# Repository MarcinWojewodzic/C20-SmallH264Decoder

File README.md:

# C20 — H.264 decoding on STM32

C20 is an embedded video project built around a custom STM32H753 board and a software H.264/AVC decoder written from scratch. The first goal is to decode a short, low-resolution clip and display it on the board's LCD. From there, the project will measure how far the Cortex-M7 and external SDRAM can take it.

**Project status:** KiCad hardware design and STM32Cube firmware scaffolding are in the repository. The H.264 decoder and playback pipeline are planned.

## Hardware

Board revision **C20W1B1V1.0** pairs the STM32H753 with external SDRAM for decoded pictures and display buffers, and a touch display driven by the MCU's LCD controller.

| Subsystem | Schematic design |
| --- | --- |
| Microcontroller | STM32H753IITx, Arm Cortex-M7, with an STDC14 debug connector |
| Working memory | 16 MiB ISSI IS45S32400J SDR SDRAM on a 32-bit FMC bus |
| Display | Newhaven NHD-4.0-480480AF-ASXP-CTP, a 4-inch 480 × 480 capacitive-touch LCD with parallel RGB driven by LTDC |
| Nonvolatile memory | 32 MiB Winbond W25R256JVEIQ Quad-SPI NOR flash and FM24CL04B I²C FRAM |
| Audio | MAX98357A digital-input Class-D speaker amplifier |
| Sensors | LSM6DSV80X IMU, MMC5983MA magnetometer, and BME280 temperature, humidity, and pressure sensor |

## Decoder roadmap

1. **Bring up the video hardware.** Verify SDRAM reads and writes, then display a test pattern from an SDRAM framebuffer through LTDC.
2. **Decode a first frame.** Start with a small Annex B H.264 elementary stream. Parse NAL units and parameter sets, reconstruct an intra-coded picture from a controlled test stream, and compare the decoded pixels with a reference decoder.
3. **Play a short clip.** Add P-slice decoding, motion compensation, and reference picture management. Convert the decoded frames into a display framebuffer and show them on the LCD.
4. **Measure performance on the board.** Track decode time per frame and peak memory use while LTDC scans out the framebuffer. Use those measurements to determine practical resolution and frame-rate targets.

H.265/HEVC is a tentative follow-up. Once H.264 playback can be profiled on the board, the measurements can inform a feasibility study for a limited HEVC decoding experiment.

## Open the project

- **Hardware** — Open the [KiCad project](Hardware/C20W1B1V1.0/KiCad/C20W1B1V1.0.kicad_pro) to browse the [schematic](Hardware/C20W1B1V1.0/KiCad/C20W1B1V1.0.kicad_sch) and [PCB layout](Hardware/C20W1B1V1.0/KiCad/C20W1B1V1.0.kicad_pcb).
- **Firmware** — Import [Software/C20](Software/C20/) as an existing STM32CubeIDE project. The [CubeMX configuration](Software/C20/C20.ioc) defines the MCU and peripheral setup.

## AI assistance

I use OpenAI Codex as a reviewer. It helps me review schematics, question assumptions, and edit documentation. I make the architecture and implementation decisions myself. I'm building C20 for fun and to learn how video decoding works on a microcontroller. I measure performance to understand what the hardware can do and where it runs out of headroom.

## License

The project is released under the [MIT License](LICENSE).

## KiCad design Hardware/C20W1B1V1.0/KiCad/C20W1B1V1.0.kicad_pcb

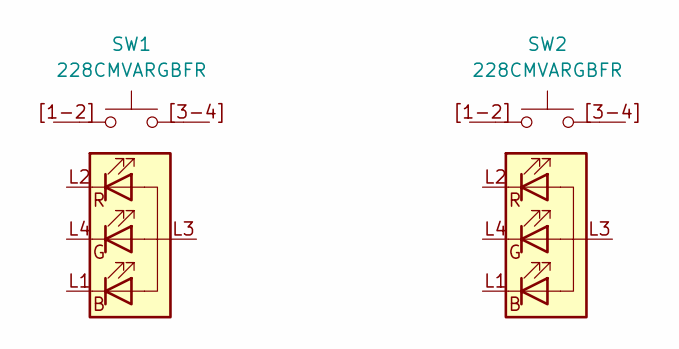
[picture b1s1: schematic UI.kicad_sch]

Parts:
SW1, SW2: 228CMVARGBFR

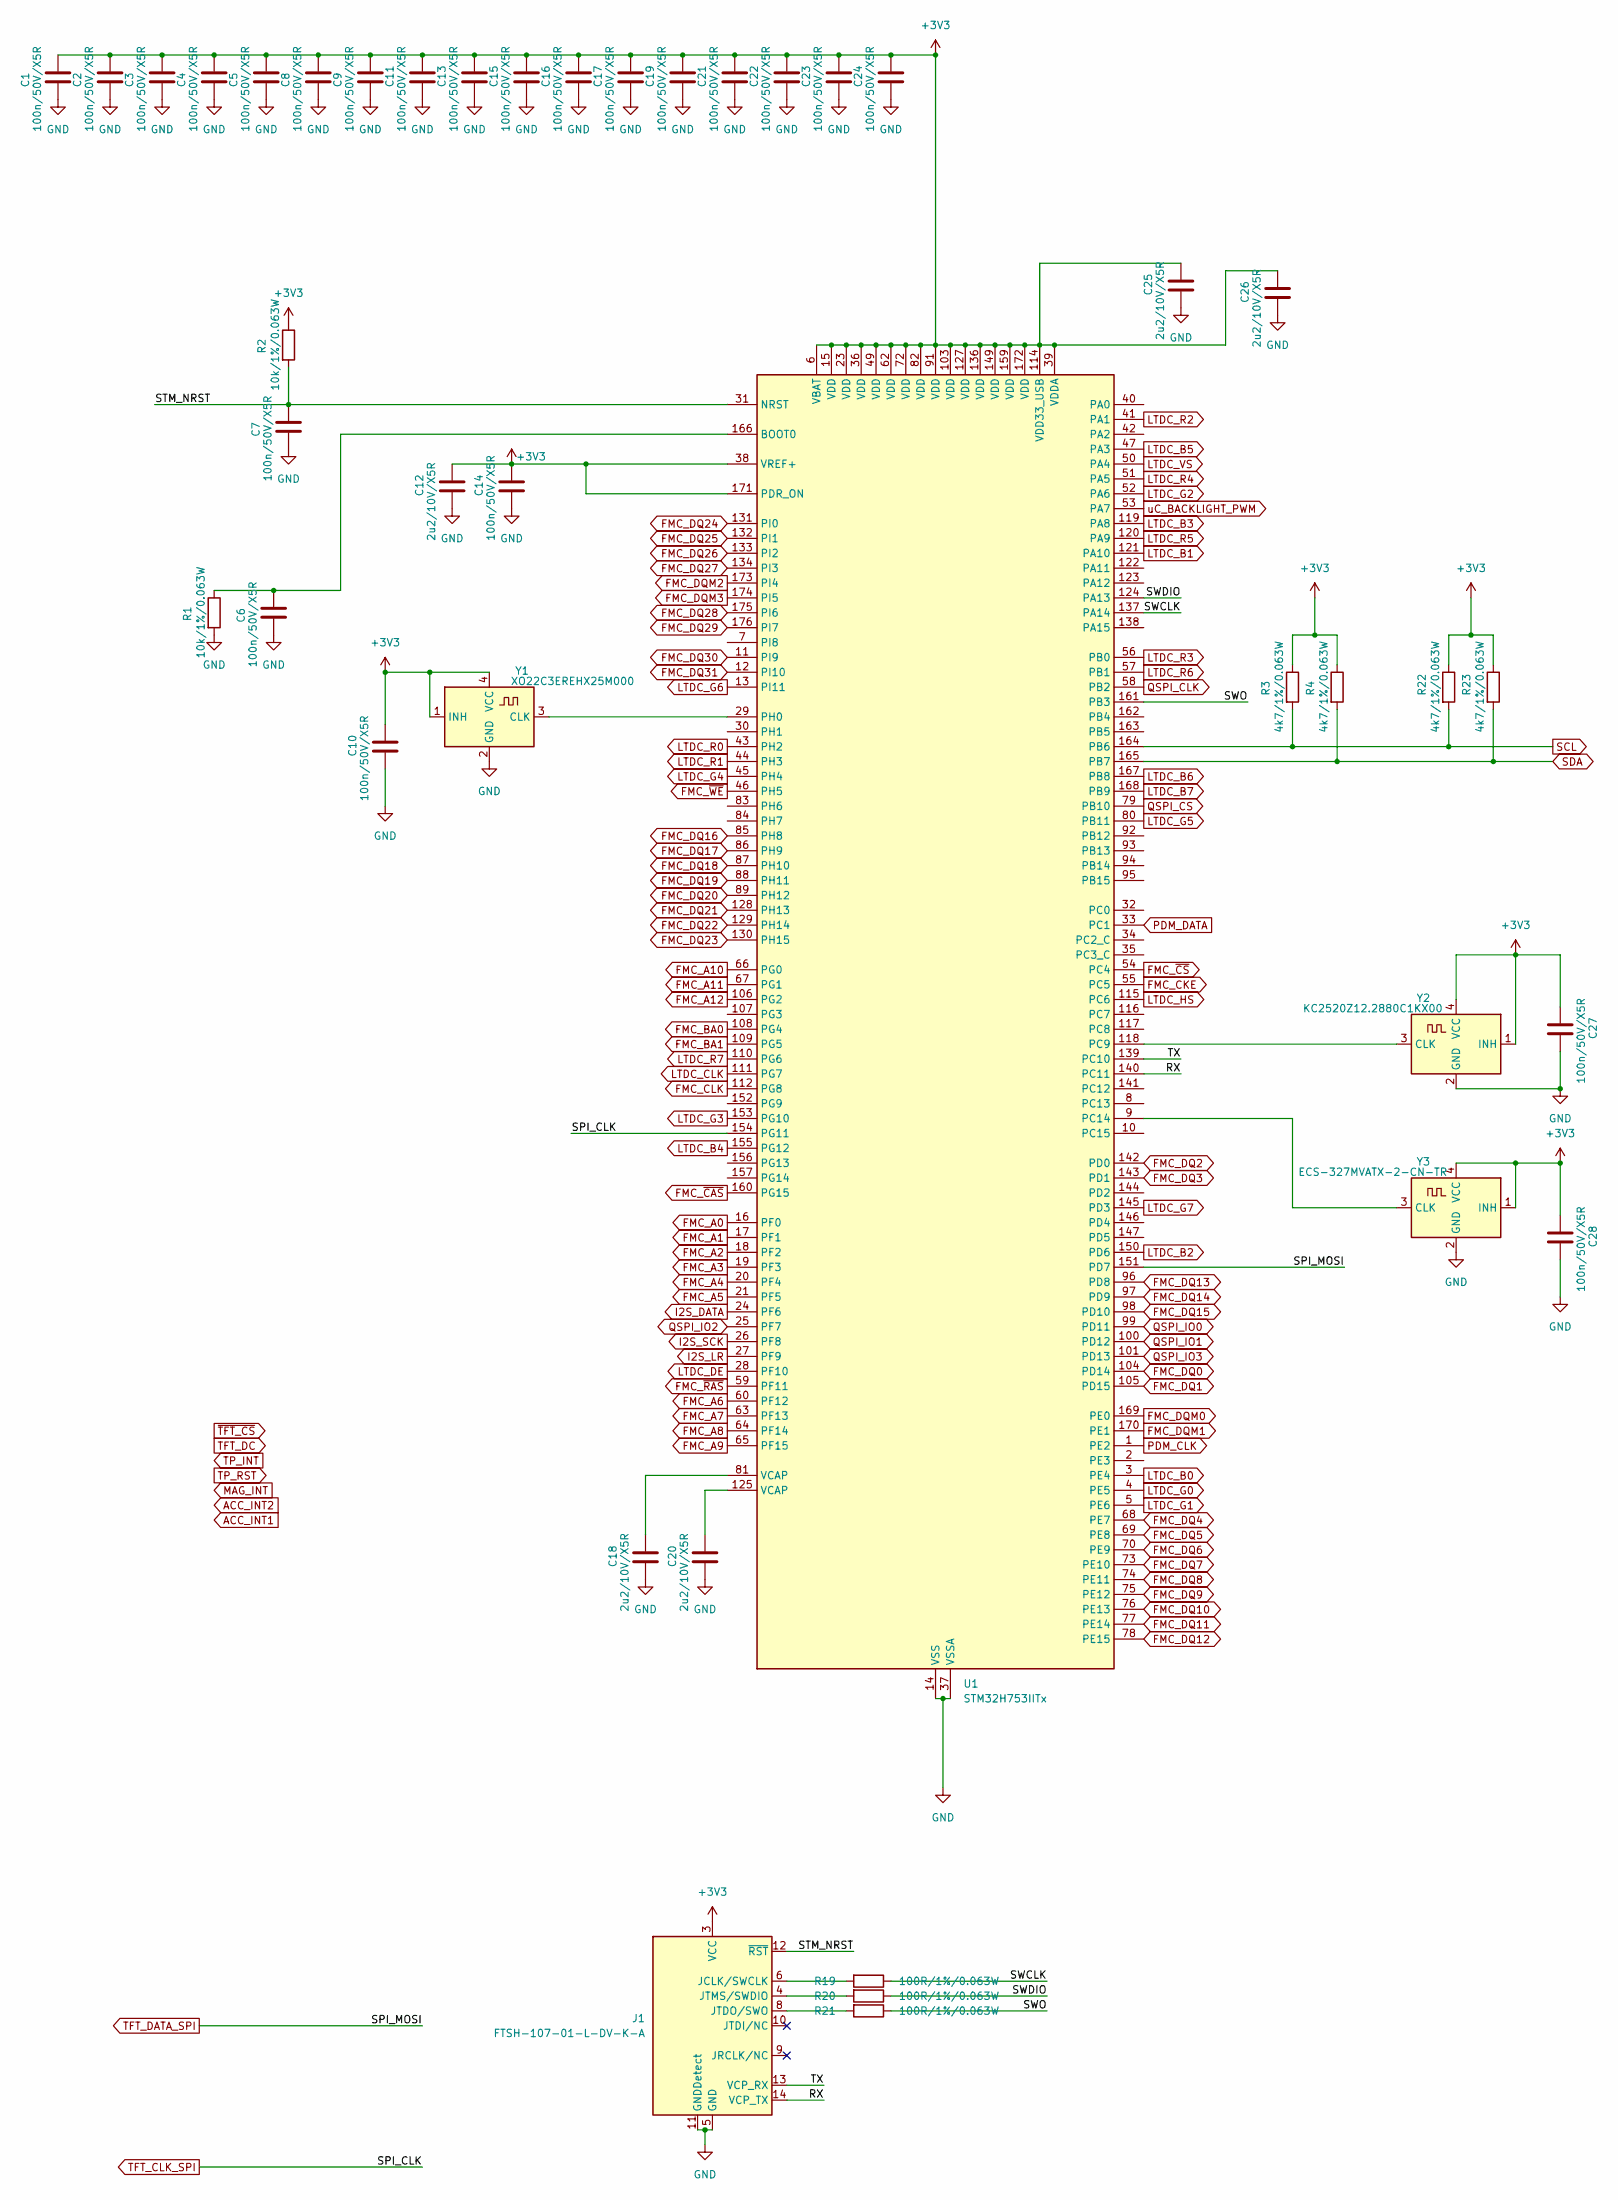
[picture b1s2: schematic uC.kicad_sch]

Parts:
C1, C2, C3, C4, C5, C6, C7, C8, C9, C10, C11, C13, C14, C15, C16, C17, C19, C21, C22, C23, C24, C27, C28: 100n/50V/X5R; C_0402_1005Metric
C12, C18, C20, C25, C26: 2u2/10V/X5R; C_0402_1005Metric
J1: FTSH-107-01-L-DV-K-A; SAMTEC_FTSH-107-01-L-DV-K-A
R1, R2: 10k/1%/0.063W; R_0402_1005Metric
R3, R4, R22, R23: 4k7/1%/0.063W; R_0402_1005Metric
R19, R20, R21: 100R/1%/0.063W; R_0402_1005Metric
U1: STM32H753IITx; LQFP-176_24x24mm_P0.5mm
Y1: XO22C3EREHX25M000; Oscillator_SMD_Kyocera_KC2520Z-4Pin_2.5x2.0mm
Y2: KC2520Z12.2880C1KX00; Oscillator_SMD_Kyocera_KC2520Z-4Pin_2.5x2.0mm
Y3: ECS-327MVATX-2-CN-TR; Oscillator_SMD_Kyocera_KC2520Z-4Pin_2.5x2.0mm

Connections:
+3V3: C1.1, C2.1, C3.1, C4.1, C5.1, C8.1, C9.1, C10.1, C11.1, C12.1, C13.1, C14.1, C15.1, C16.1, C17.1, C19.1, C21.1, C22.1, C23.1, C24.1, C25.1, C26.1, C27.1, C28.1, J1.3 (VCC), R2.1, R3.1, R4.1, R22.1, R23.1, U1.6 (VBAT), U1.15 (VDD), U1.23 (VDD), U1.36 (VDD), U1.38 (VREF+), U1.39 (VDDA), U1.49 (VDD), U1.62 (VDD), U1.72 (VDD), U1.82 (VDD), U1.91 (VDD), U1.103 (VDD), U1.114 (VDD33_USB), U1.127 (VDD), U1.136 (VDD), U1.149 (VDD), U1.159 (VDD), U1.171 (PDR_ON), U1.172 (VDD), Y1.1 (INH), Y1.4 (VCC), Y2.1 (INH), Y2.4 (VCC), Y3.1 (INH), Y3.4 (VCC); also elsewhere on the board
/uC/RX: J1.14 (VCP_TX), U1.140 (PC11)
/uC/STM_NRST: C7.1, J1.12 (~RST), R2.2, U1.31 (NRST)
/uC/SWCLK: R19.1, U1.137 (PA14)
/uC/SWDIO: R20.1, U1.124 (PA13)
/uC/SWO: R21.1, U1.161 (PB3)
/uC/TX: J1.13 (VCP_RX), U1.139 (PC10)
FMC_A0: U1.16 (PF0); also elsewhere on the board
FMC_A1: U1.17 (PF1); also elsewhere on the board
FMC_A2: U1.18 (PF2); also elsewhere on the board
FMC_A3: U1.19 (PF3); also elsewhere on the board
FMC_A4: U1.20 (PF4); also elsewhere on the board
FMC_A5: U1.21 (PF5); also elsewhere on the board
FMC_A6: U1.60 (PF12); also elsewhere on the board
FMC_A7: U1.63 (PF13); also elsewhere on the board
FMC_A8: U1.64 (PF14); also elsewhere on the board
FMC_A9: U1.65 (PF15); also elsewhere on the board
FMC_A10: U1.66 (PG0); also elsewhere on the board
FMC_A11: U1.67 (PG1); also elsewhere on the board
FMC_A12: U1.106 (PG2); also elsewhere on the board
FMC_BA0: U1.108 (PG4); also elsewhere on the board
FMC_BA1: U1.109 (PG5); also elsewhere on the board
FMC_CKE: U1.55 (PC5); also elsewhere on the board
FMC_CLK: U1.112 (PG8); also elsewhere on the board
FMC_DQ0: U1.104 (PD14); also elsewhere on the board
FMC_DQ1: U1.105 (PD15); also elsewhere on the board
FMC_DQ2: U1.142 (PD0); also elsewhere on the board
FMC_DQ3: U1.143 (PD1); also elsewhere on the board
FMC_DQ4: U1.68 (PE7); also elsewhere on the board
FMC_DQ5: U1.69 (PE8); also elsewhere on the board
FMC_DQ6: U1.70 (PE9); also elsewhere on the board
FMC_DQ7: U1.73 (PE10); also elsewhere on the board
FMC_DQ8: U1.74 (PE11); also elsewhere on the board
FMC_DQ9: U1.75 (PE12); also elsewhere on the board
FMC_DQ10: U1.76 (PE13); also elsewhere on the board
FMC_DQ11: U1.77 (PE14); also elsewhere on the board
FMC_DQ12: U1.78 (PE15); also elsewhere on the board
FMC_DQ13: U1.96 (PD8); also elsewhere on the board
FMC_DQ14: U1.97 (PD9); also elsewhere on the board
FMC_DQ15: U1.98 (PD10); also elsewhere on the board
FMC_DQ16: U1.85 (PH8); also elsewhere on the board
FMC_DQ17: U1.86 (PH9); also elsewhere on the board
FMC_DQ18: U1.87 (PH10); also elsewhere on the board
FMC_DQ19: U1.88 (PH11); also elsewhere on the board
FMC_DQ20: U1.89 (PH12); also elsewhere on the board
FMC_DQ21: U1.128 (PH13); also elsewhere on the board
FMC_DQ22: U1.129 (PH14); also elsewhere on the board
FMC_DQ23: U1.130 (PH15); also elsewhere on the board
FMC_DQ24: U1.131 (PI0); also elsewhere on the board
FMC_DQ25: U1.132 (PI1); also elsewhere on the board
FMC_DQ26: U1.133 (PI2); also elsewhere on the board
FMC_DQ27: U1.134 (PI3); also elsewhere on the board
FMC_DQ28: U1.175 (PI6); also elsewhere on the board
FMC_DQ29: U1.176 (PI7); also elsewhere on the board
FMC_DQ30: U1.11 (PI9); also elsewhere on the board
FMC_DQ31: U1.12 (PI10); also elsewhere on the board
FMC_DQM0: U1.169 (PE0); also elsewhere on the board
FMC_DQM1: U1.170 (PE1); also elsewhere on the board
FMC_DQM2: U1.173 (PI4); also elsewhere on the board
FMC_DQM3: U1.174 (PI5); also elsewhere on the board
FMC_~CAS: U1.160 (PG15); also elsewhere on the board
FMC_~CS: U1.54 (PC4); also elsewhere on the board
FMC_~RAS: U1.59 (PF11); also elsewhere on the board
FMC_~WE: U1.46 (PH5); also elsewhere on the board
GND: C1.2, C2.2, C3.2, C4.2, C5.2, C6.2, C7.2, C8.2, C9.2, C10.2, C11.2, C12.2, C13.2, C14.2, C15.2, C16.2, C17.2, C18.2, C19.2, C20.2, C21.2, C22.2, C23.2, C24.2, C25.2, C26.2, C27.2, C28.2, J1.5 (GND), J1.7 (GND), J1.11 (GNDDetect), R1.2, U1.14 (VSS), U1.22 (VSS), U1.37 (VSSA), U1.48 (VSS), U1.61 (VSS), U1.71 (VSS), U1.90 (VSS), U1.102 (VSS), U1.113 (VSS), U1.126 (VSS), U1.135 (VSS), U1.148 (VSS), U1.158 (VSS), Y1.2 (GND), Y2.2 (GND), Y3.2 (GND); also elsewhere on the board
I2S_DATA: U1.24 (PF6); also elsewhere on the board
I2S_LR: U1.27 (PF9); also elsewhere on the board
I2S_SCK: U1.26 (PF8); also elsewhere on the board
LTDC_B0: U1.3 (PE4); also elsewhere on the board
LTDC_B1: U1.121 (PA10); also elsewhere on the board
LTDC_B2: U1.150 (PD6); also elsewhere on the board
LTDC_B3: U1.119 (PA8); also elsewhere on the board
LTDC_B4: U1.155 (PG12); also elsewhere on the board
LTDC_B5: U1.47 (PA3); also elsewhere on the board
LTDC_B6: U1.167 (PB8); also elsewhere on the board
LTDC_B7: U1.168 (PB9); also elsewhere on the board
LTDC_CLK: U1.111 (PG7); also elsewhere on the board
LTDC_DE: U1.28 (PF10); also elsewhere on the board
LTDC_G0: U1.4 (PE5); also elsewhere on the board
LTDC_G1: U1.5 (PE6); also elsewhere on the board
LTDC_G2: U1.52 (PA6); also elsewhere on the board
LTDC_G3: U1.153 (PG10); also elsewhere on the board
LTDC_G4: U1.45 (PH4); also elsewhere on the board
LTDC_G5: U1.80 (PB11); also elsewhere on the board
LTDC_G6: U1.13 (PI11); also elsewhere on the board
LTDC_G7: U1.145 (PD3); also elsewhere on the board
LTDC_HS: U1.115 (PC6); also elsewhere on the board
LTDC_R0: U1.43 (PH2); also elsewhere on the board
LTDC_R1: U1.44 (PH3); also elsewhere on the board
LTDC_R2: U1.41 (PA1); also elsewhere on the board
LTDC_R3: U1.56 (PB0); also elsewhere on the board
LTDC_R4: U1.51 (PA5); also elsewhere on the board
LTDC_R5: U1.120 (PA9); also elsewhere on the board
LTDC_R6: U1.57 (PB1); also elsewhere on the board
LTDC_R7: U1.110 (PG6); also elsewhere on the board
LTDC_VS: U1.50 (PA4); also elsewhere on the board
unnamed: C18.1, U1.81 (VCAP)
unnamed: C20.1, U1.125 (VCAP)
unnamed: J1.6 (JCLK/SWCLK), R19.2
unnamed: J1.8 (JTDO/SWO), R21.2
unnamed: J1.4 (JTMS/SWDIO), R20.2
unnamed: C6.1, R1.1, U1.166 (BOOT0)
unnamed: U1.118 (PC9), Y2.3 (CLK)
unnamed: U1.9 (PC14), Y3.3 (CLK)
unnamed: U1.29 (PH0), Y1.3 (CLK)
PDM_CLK: U1.1 (PE2); also elsewhere on the board
PDM_DATA: U1.33 (PC1); also elsewhere on the board
QSPI_CLK: U1.58 (PB2); also elsewhere on the board
QSPI_CS: U1.79 (PB10); also elsewhere on the board
QSPI_IO0: U1.99 (PD11); also elsewhere on the board
QSPI_IO1: U1.100 (PD12); also elsewhere on the board
QSPI_IO2: U1.25 (PF7); also elsewhere on the board
QSPI_IO3: U1.101 (PD13); also elsewhere on the board
SCL: R3.2, R22.2, U1.164 (PB6); also elsewhere on the board
SDA: R4.2, R23.2, U1.165 (PB7); also elsewhere on the board
TFT_CLK_SPI: U1.154 (PG11); also elsewhere on the board
TFT_DATA_SPI: U1.151 (PD7); also elsewhere on the board
uC_BACKLIGHT_PWM: U1.53 (PA7); also elsewhere on the board

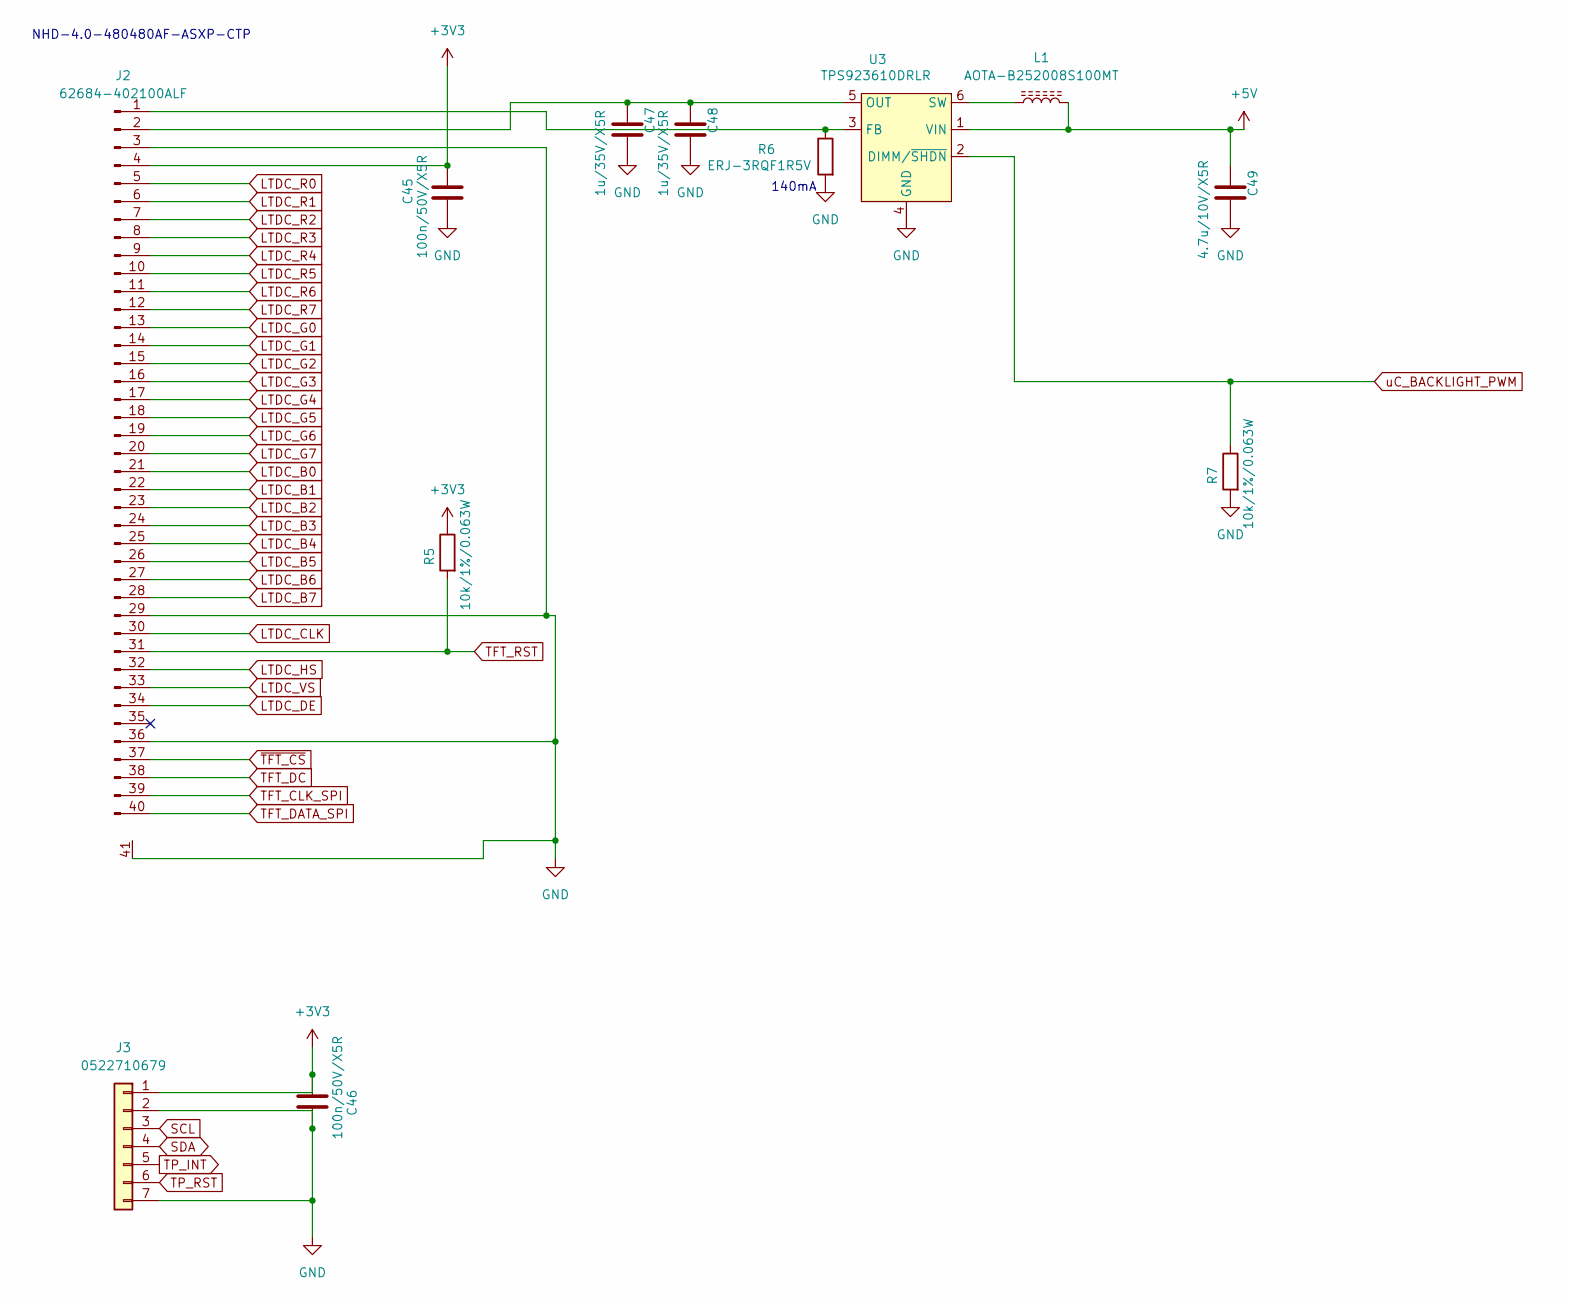
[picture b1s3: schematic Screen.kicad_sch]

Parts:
C45, C46: 100n/50V/X5R; C_0402_1005Metric
C47, C48: 1u/35V/X5R; C_0805_2012Metric
C49: 4.7u/10V/X5R; C_0402_1005Metric
J2: 62684-402100ALF; AMPHENOL_62684-402100ALF
J3: 0522710679; CON_522710679_MOL
L1: AOTA-B252008S100MT; L_1008_2520Metric
R5, R7: 10k/1%/0.063W; R_0402_1005Metric
R6: ERJ-3RQF1R5V; R_0603_1608Metric
U3: TPS923610DRLR; SOT-563

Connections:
+3V3: C45.1, C46.2, J2.4, J3.1, R5.1; also elsewhere on the board
+5V: C49.1, L1.1, U3.1 (VIN); also elsewhere on the board
GND: C45.2, C46.1, C47.2, C48.2, C49.2, J2.3, J2.29, J2.36, J2.41 (MH), J3.2, J3.7, R6.2, R7.2, U3.4 (GND); also elsewhere on the board
LTDC_B0: J2.21; also elsewhere on the board
LTDC_B1: J2.22; also elsewhere on the board
LTDC_B2: J2.23; also elsewhere on the board
LTDC_B3: J2.24; also elsewhere on the board
LTDC_B4: J2.25; also elsewhere on the board
LTDC_B5: J2.26; also elsewhere on the board
LTDC_B6: J2.27; also elsewhere on the board
LTDC_B7: J2.28; also elsewhere on the board
LTDC_CLK: J2.30; also elsewhere on the board
LTDC_DE: J2.34; also elsewhere on the board
LTDC_G0: J2.13; also elsewhere on the board
LTDC_G1: J2.14; also elsewhere on the board
LTDC_G2: J2.15; also elsewhere on the board
LTDC_G3: J2.16; also elsewhere on the board
LTDC_G4: J2.17; also elsewhere on the board
LTDC_G5: J2.18; also elsewhere on the board
LTDC_G6: J2.19; also elsewhere on the board
LTDC_G7: J2.20; also elsewhere on the board
LTDC_HS: J2.32; also elsewhere on the board
LTDC_R0: J2.5; also elsewhere on the board
LTDC_R1: J2.6; also elsewhere on the board
LTDC_R2: J2.7; also elsewhere on the board
LTDC_R3: J2.8; also elsewhere on the board
LTDC_R4: J2.9; also elsewhere on the board
LTDC_R5: J2.10; also elsewhere on the board
LTDC_R6: J2.11; also elsewhere on the board
LTDC_R7: J2.12; also elsewhere on the board
LTDC_VS: J2.33; also elsewhere on the board
unnamed: J2.1, R6.1, U3.3 (FB)
unnamed: C47.1, C48.1, J2.2, U3.5 (OUT)
unnamed: L1.2, U3.6 (SW)
SCL: J3.3; also elsewhere on the board
SDA: J3.4; also elsewhere on the board
TFT_CLK_SPI: J2.39; also elsewhere on the board
TFT_DATA_SPI: J2.40; also elsewhere on the board
TFT_DC: J2.38
TFT_RST: J2.31, R5.2
TP_INT: J3.5
TP_RST: J3.6
uC_BACKLIGHT_PWM: R7.1, U3.2 (DIMM/~SHDN); also elsewhere on the board
~TFT_CS: J2.37

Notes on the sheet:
NHD-4.0-480480AF-ASXP-CTP
140mA

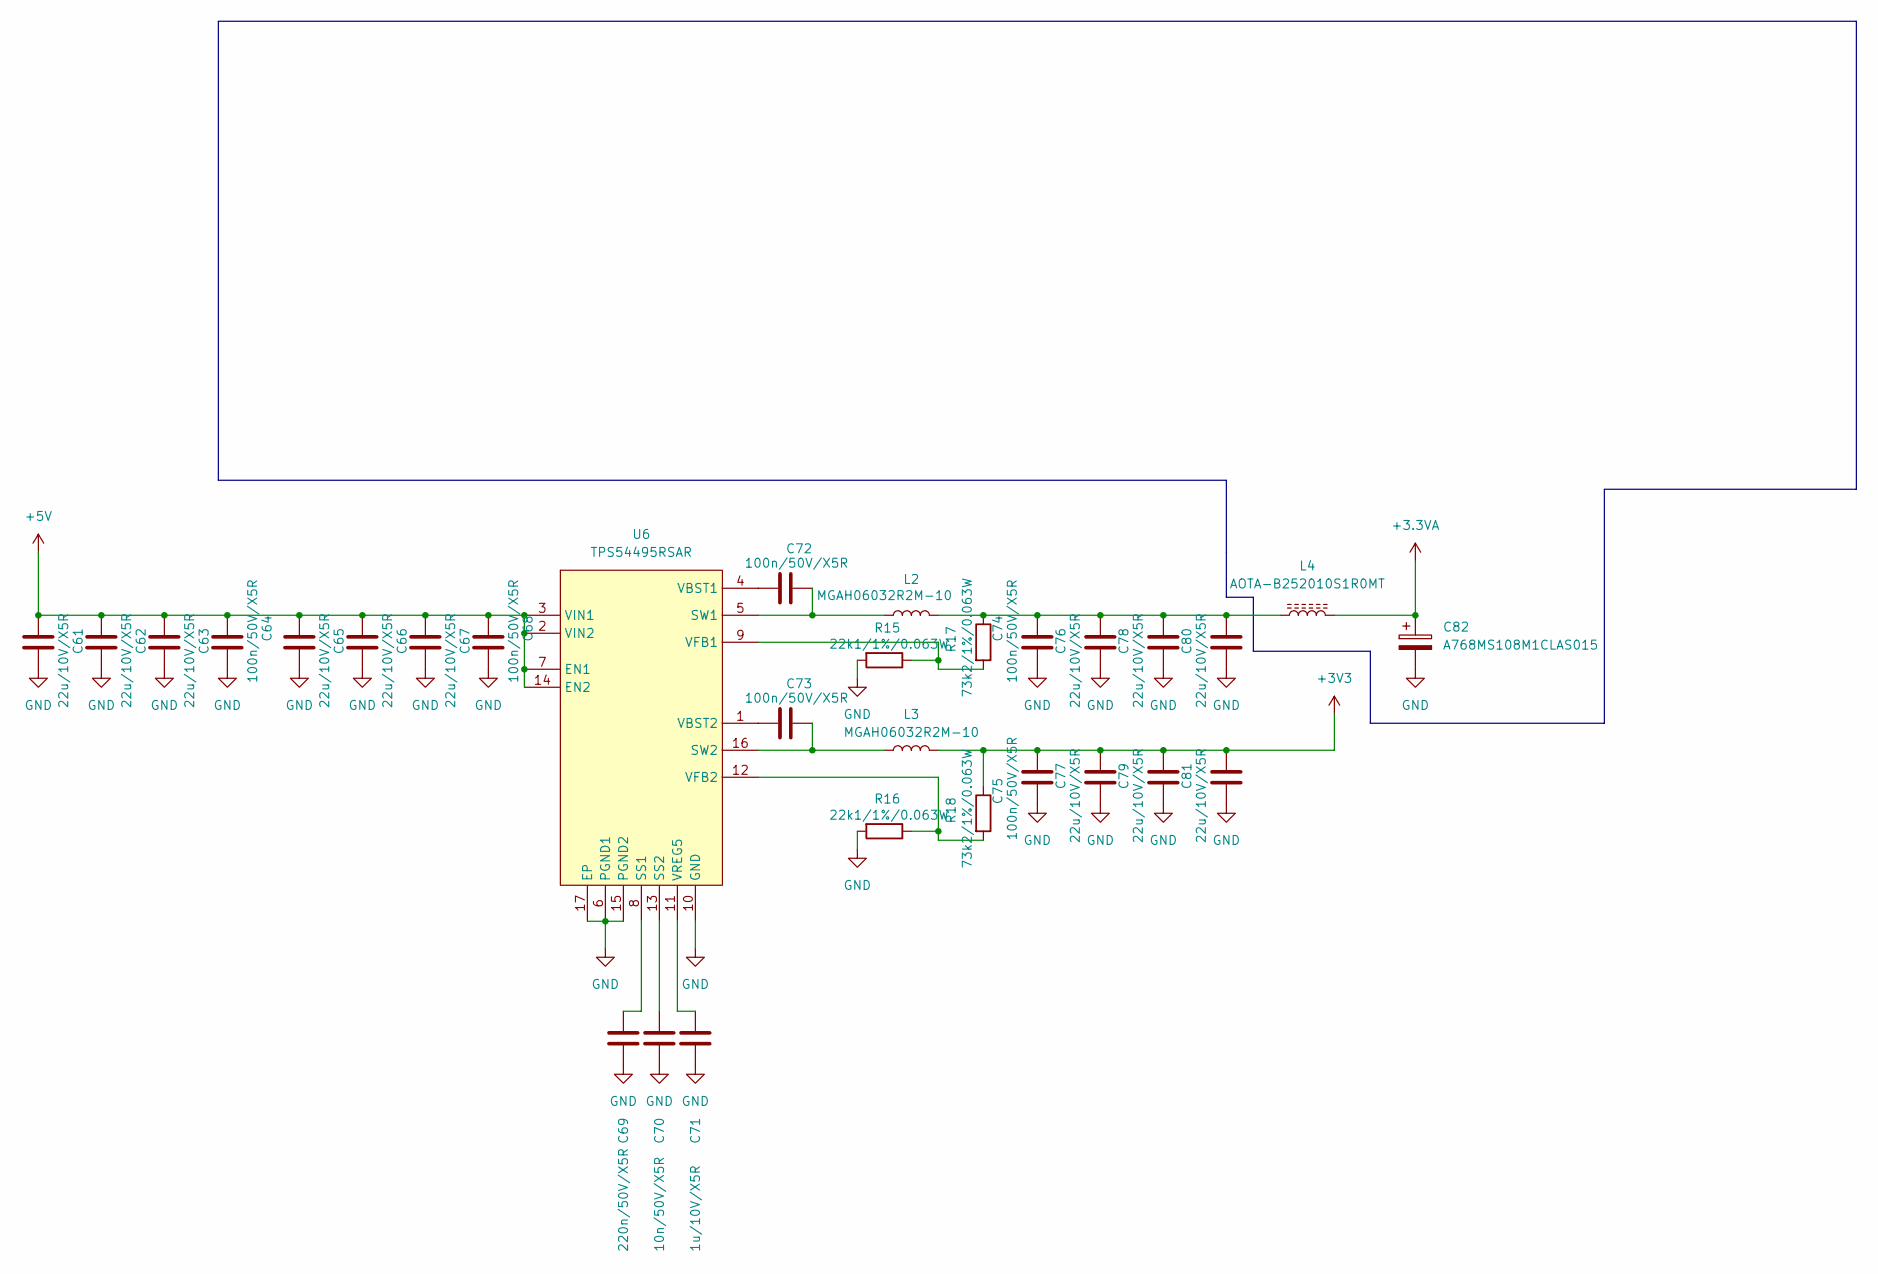
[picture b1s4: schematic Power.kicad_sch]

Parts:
C61, C62, C63, C65, C66, C67, C76, C77, C78, C79, C80, C81: 22u/10V/X5R; C_0603_1608Metric
C64, C68, C72, C73, C74, C75: 100n/50V/X5R; C_0402_1005Metric
C69: 220n/50V/X5R; C_0402_1005Metric
C70: 10n/50V/X5R; C_0402_1005Metric
C71: 1u/10V/X5R; C_0402_1005Metric
C82: A768MS108M1CLAS015; CP_Elec_10x12.6
L2, L3: MGAH06032R2M-10; MGAH06032R2M10
L4: AOTA-B252010S1R0MT; L_1008_2520Metric
R15, R16: 22k1/1%/0.063W; R_0402_1005Metric
R17, R18: 73k2/1%/0.063W; R_0402_1005Metric
U6: TPS54495RSAR; Texas_RSA_VQFN-16-1EP_4x4mm_P0.65mm_EP2.7x2.7mm; Manufacturer_Part_Number TPS54495RSAR; Mouser Part Number 595-TPS54495RSAR

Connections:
+3.3VA: C82.1, L4.1; also elsewhere on the board
+3V3: C75.2, C77.1, C79.1, C81.1, L3.2, R18.1; also elsewhere on the board
+5V: C61.1, C62.1, C63.1, C64.1, C65.1, C66.1, C67.1, C68.1, U6.2 (VIN2), U6.3 (VIN1), U6.7 (EN1), U6.14 (EN2); also elsewhere on the board
GND: C61.2, C62.2, C63.2, C64.2, C65.2, C66.2, C67.2, C68.2, C69.2, C70.2, C71.2, C74.2, C75.1, C76.2, C77.2, C78.2, C79.2, C80.2, C81.2, C82.2, R15.2, R16.2, U6.6 (PGND1), U6.10 (GND), U6.15 (PGND2), U6.17 (EP); also elsewhere on the board
unnamed: C74.1, C76.1, C78.1, C80.1, L2.2, L4.2, R17.1
unnamed: C69.1, U6.8 (SS1)
unnamed: C70.1, U6.13 (SS2)
unnamed: C72.1, L2.1, U6.5 (SW1)
unnamed: C73.1, L3.1, U6.16 (SW2)
unnamed: C72.2, U6.4 (VBST1)
unnamed: C73.2, U6.1 (VBST2)
unnamed: R15.1, R17.2, U6.9 (VFB1)
unnamed: R16.1, R18.2, U6.12 (VFB2)
unnamed: C71.1, U6.11 (VREG5)

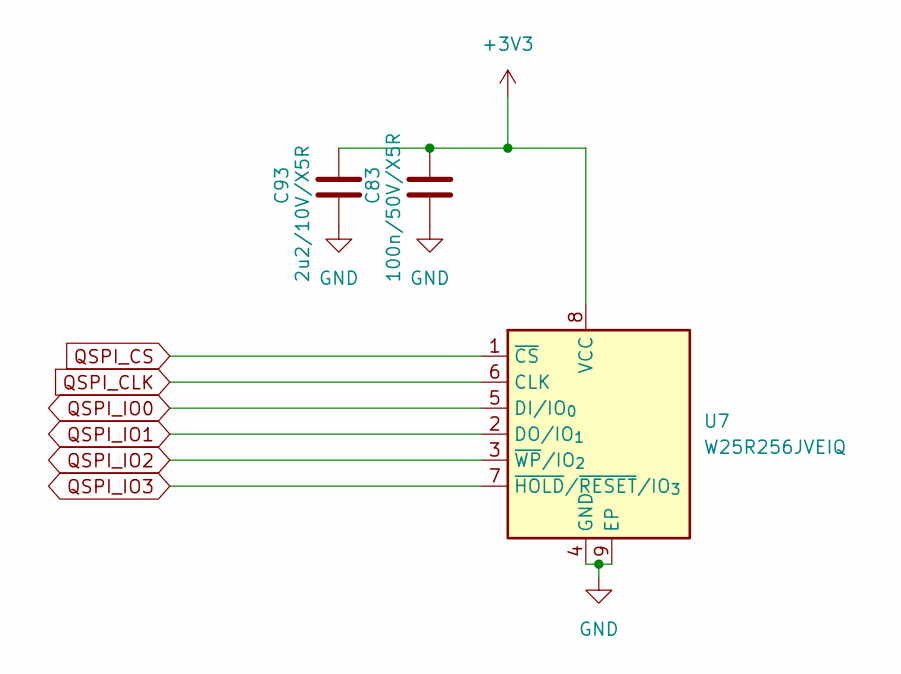
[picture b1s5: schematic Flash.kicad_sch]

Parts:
C83: 100n/50V/X5R; C_0402_1005Metric
C93: 2u2/10V/X5R; C_0402_1005Metric
U7: W25R256JVEIQ; WSON-8-1EP_8x6mm_P1.27mm_EP3.4x4.3mm

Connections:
+3V3: C83.1, C93.1, U7.8 (VCC); also elsewhere on the board
GND: C83.2, C93.2, U7.4 (GND), U7.9 (EP); also elsewhere on the board
QSPI_CLK: U7.6 (CLK); also elsewhere on the board
QSPI_CS: U7.1 (~CS); also elsewhere on the board
QSPI_IO0: U7.5 (DI/IO_{0}); also elsewhere on the board
QSPI_IO1: U7.2 (DO/IO_{1}); also elsewhere on the board
QSPI_IO2: U7.3 (~WP/IO_{2}); also elsewhere on the board
QSPI_IO3: U7.7 (~HOLD/~RESET/IO_{3}); also elsewhere on the board

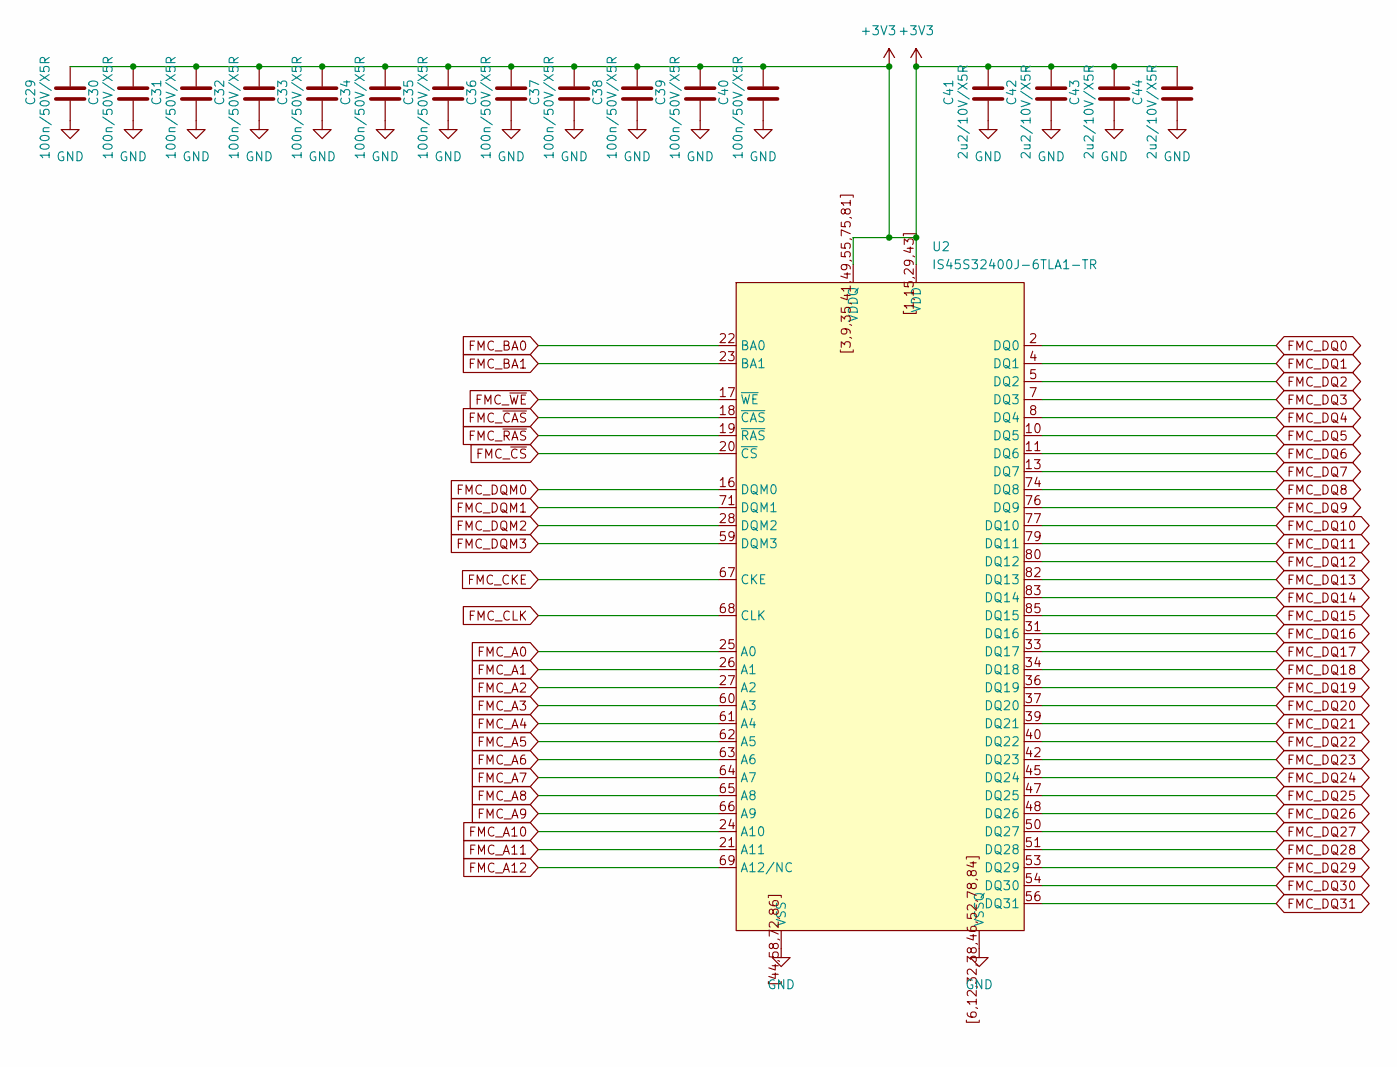
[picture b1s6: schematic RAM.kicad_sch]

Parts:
C29, C30, C31, C32, C33, C34, C35, C36, C37, C38, C39, C40: 100n/50V/X5R; C_0402_1005Metric
C41, C42, C43, C44: 2u2/10V/X5R; C_0402_1005Metric
U2: IS45S32400J-6TLA1-TR; TSOP-II-86_10.16x22.22mm_P0.5mm_ISSI

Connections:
+3V3: C29.1, C30.1, C31.1, C32.1, C33.1, C34.1, C35.1, C36.1, C37.1, C38.1, C39.1, C40.1, C41.1, C42.1, C43.1, C44.1, U2.1 (VDD), U2.3 (VDDQ), U2.9 (VDDQ), U2.15 (VDD), U2.29 (VDD), U2.35 (VDDQ), U2.41 (VDDQ), U2.43 (VDD), U2.49 (VDDQ), U2.55 (VDDQ), U2.75 (VDDQ), U2.81 (VDDQ), U2.[1,15,29,43] (VDD), U2.[3,9,35,41,49,55,75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 (VDDQ); also elsewhere on the board
FMC_A0: U2.25 (A0); also elsewhere on the board
FMC_A1: U2.26 (A1); also elsewhere on the board
FMC_A2: U2.27 (A2); also elsewhere on the board
FMC_A3: U2.60 (A3); also elsewhere on the board
FMC_A4: U2.61 (A4); also elsewhere on the board
FMC_A5: U2.62 (A5); also elsewhere on the board
FMC_A6: U2.63 (A6); also elsewhere on the board
FMC_A7: U2.64 (A7); also elsewhere on the board
FMC_A8: U2.65 (A8); also elsewhere on the board
FMC_A9: U2.66 (A9); also elsewhere on the board
FMC_A10: U2.24 (A10); also elsewhere on the board
FMC_A11: U2.21 (A11); also elsewhere on the board
FMC_A12: U2.69 (A12/NC); also elsewhere on the board
FMC_BA0: U2.22 (BA0); also elsewhere on the board
FMC_BA1: U2.23 (BA1); also elsewhere on the board
FMC_CKE: U2.67 (CKE); also elsewhere on the board
FMC_CLK: U2.68 (CLK); also elsewhere on the board
FMC_DQ0: U2.2 (DQ0); also elsewhere on the board
FMC_DQ1: U2.4 (DQ1); also elsewhere on the board
FMC_DQ2: U2.5 (DQ2); also elsewhere on the board
FMC_DQ3: U2.7 (DQ3); also elsewhere on the board
FMC_DQ4: U2.8 (DQ4); also elsewhere on the board
FMC_DQ5: U2.10 (DQ5); also elsewhere on the board
FMC_DQ6: U2.11 (DQ6); also elsewhere on the board
FMC_DQ7: U2.13 (DQ7); also elsewhere on the board
FMC_DQ8: U2.74 (DQ8); also elsewhere on the board
FMC_DQ9: U2.76 (DQ9); also elsewhere on the board
FMC_DQ10: U2.77 (DQ10); also elsewhere on the board
FMC_DQ11: U2.79 (DQ11); also elsewhere on the board
FMC_DQ12: U2.80 (DQ12); also elsewhere on the board
FMC_DQ13: U2.82 (DQ13); also elsewhere on the board
FMC_DQ14: U2.83 (DQ14); also elsewhere on the board
FMC_DQ15: U2.85 (DQ15); also elsewhere on the board
FMC_DQ16: U2.31 (DQ16); also elsewhere on the board
FMC_DQ17: U2.33 (DQ17); also elsewhere on the board
FMC_DQ18: U2.34 (DQ18); also elsewhere on the board
FMC_DQ19: U2.36 (DQ19); also elsewhere on the board
FMC_DQ20: U2.37 (DQ20); also elsewhere on the board
FMC_DQ21: U2.39 (DQ21); also elsewhere on the board
FMC_DQ22: U2.40 (DQ22); also elsewhere on the board
FMC_DQ23: U2.42 (DQ23); also elsewhere on the board
FMC_DQ24: U2.45 (DQ24); also elsewhere on the board
FMC_DQ25: U2.47 (DQ25); also elsewhere on the board
FMC_DQ26: U2.48 (DQ26); also elsewhere on the board
FMC_DQ27: U2.50 (DQ27); also elsewhere on the board
FMC_DQ28: U2.51 (DQ28); also elsewhere on the board
FMC_DQ29: U2.53 (DQ29); also elsewhere on the board
FMC_DQ30: U2.54 (DQ30); also elsewhere on the board
FMC_DQ31: U2.56 (DQ31); also elsewhere on the board
FMC_DQM0: U2.16 (DQM0); also elsewhere on the board
FMC_DQM1: U2.71 (DQM1); also elsewhere on the board
FMC_DQM2: U2.28 (DQM2); also elsewhere on the board
FMC_DQM3: U2.59 (DQM3); also elsewhere on the board
FMC_~CAS: U2.18 (~CAS); also elsewhere on the board
FMC_~CS: U2.20 (~CS); also elsewhere on the board
FMC_~RAS: U2.19 (~RAS); also elsewhere on the board
FMC_~WE: U2.17 (~WE); also elsewhere on the board
GND: C29.2, C30.2, C31.2, C32.2, C33.2, C34.2, C35.2, C36.2, C37.2, C38.2, C39.2, C40.2, C41.2, C42.2, C43.2, C44.2, U2.6 (VSSQ), U2.12 (VSSQ), U2.32 (VSSQ), U2.38 (VSSQ), U2.44 (VSS), U2.46 (VSSQ), U2.52 (VSSQ), U2.58 (VSS), U2.72 (VSS), U2.78 (VSSQ), U2.84 (VSSQ), U2.86 (VSS), U2.[6,12,32,38,46,52,7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 (VSSQ), U2.[44,58,72,86] (VSS); also elsewhere on the board

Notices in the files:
Software/C20/Core/Src/fmc.c:
Copyright (c) 2026 STMicroelectronics.
All rights reserved.
This software is licensed under terms that can be found in the LICENSE file
